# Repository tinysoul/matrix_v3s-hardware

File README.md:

# matrix_v3s-hardware

#### 介绍
一个简单的全志 V3s 开发板，使用 KiCad 设计。（谨慎参考，尚未验证，待更新）

#### 使用说明

配合 my_kicad_lib (也可不用)，直接用 KiCad 打开。

#### 参与贡献

1.  Fork 本仓库
2.  新建 Feat_xxx 分支
3.  提交代码
4.  新建 Pull Request

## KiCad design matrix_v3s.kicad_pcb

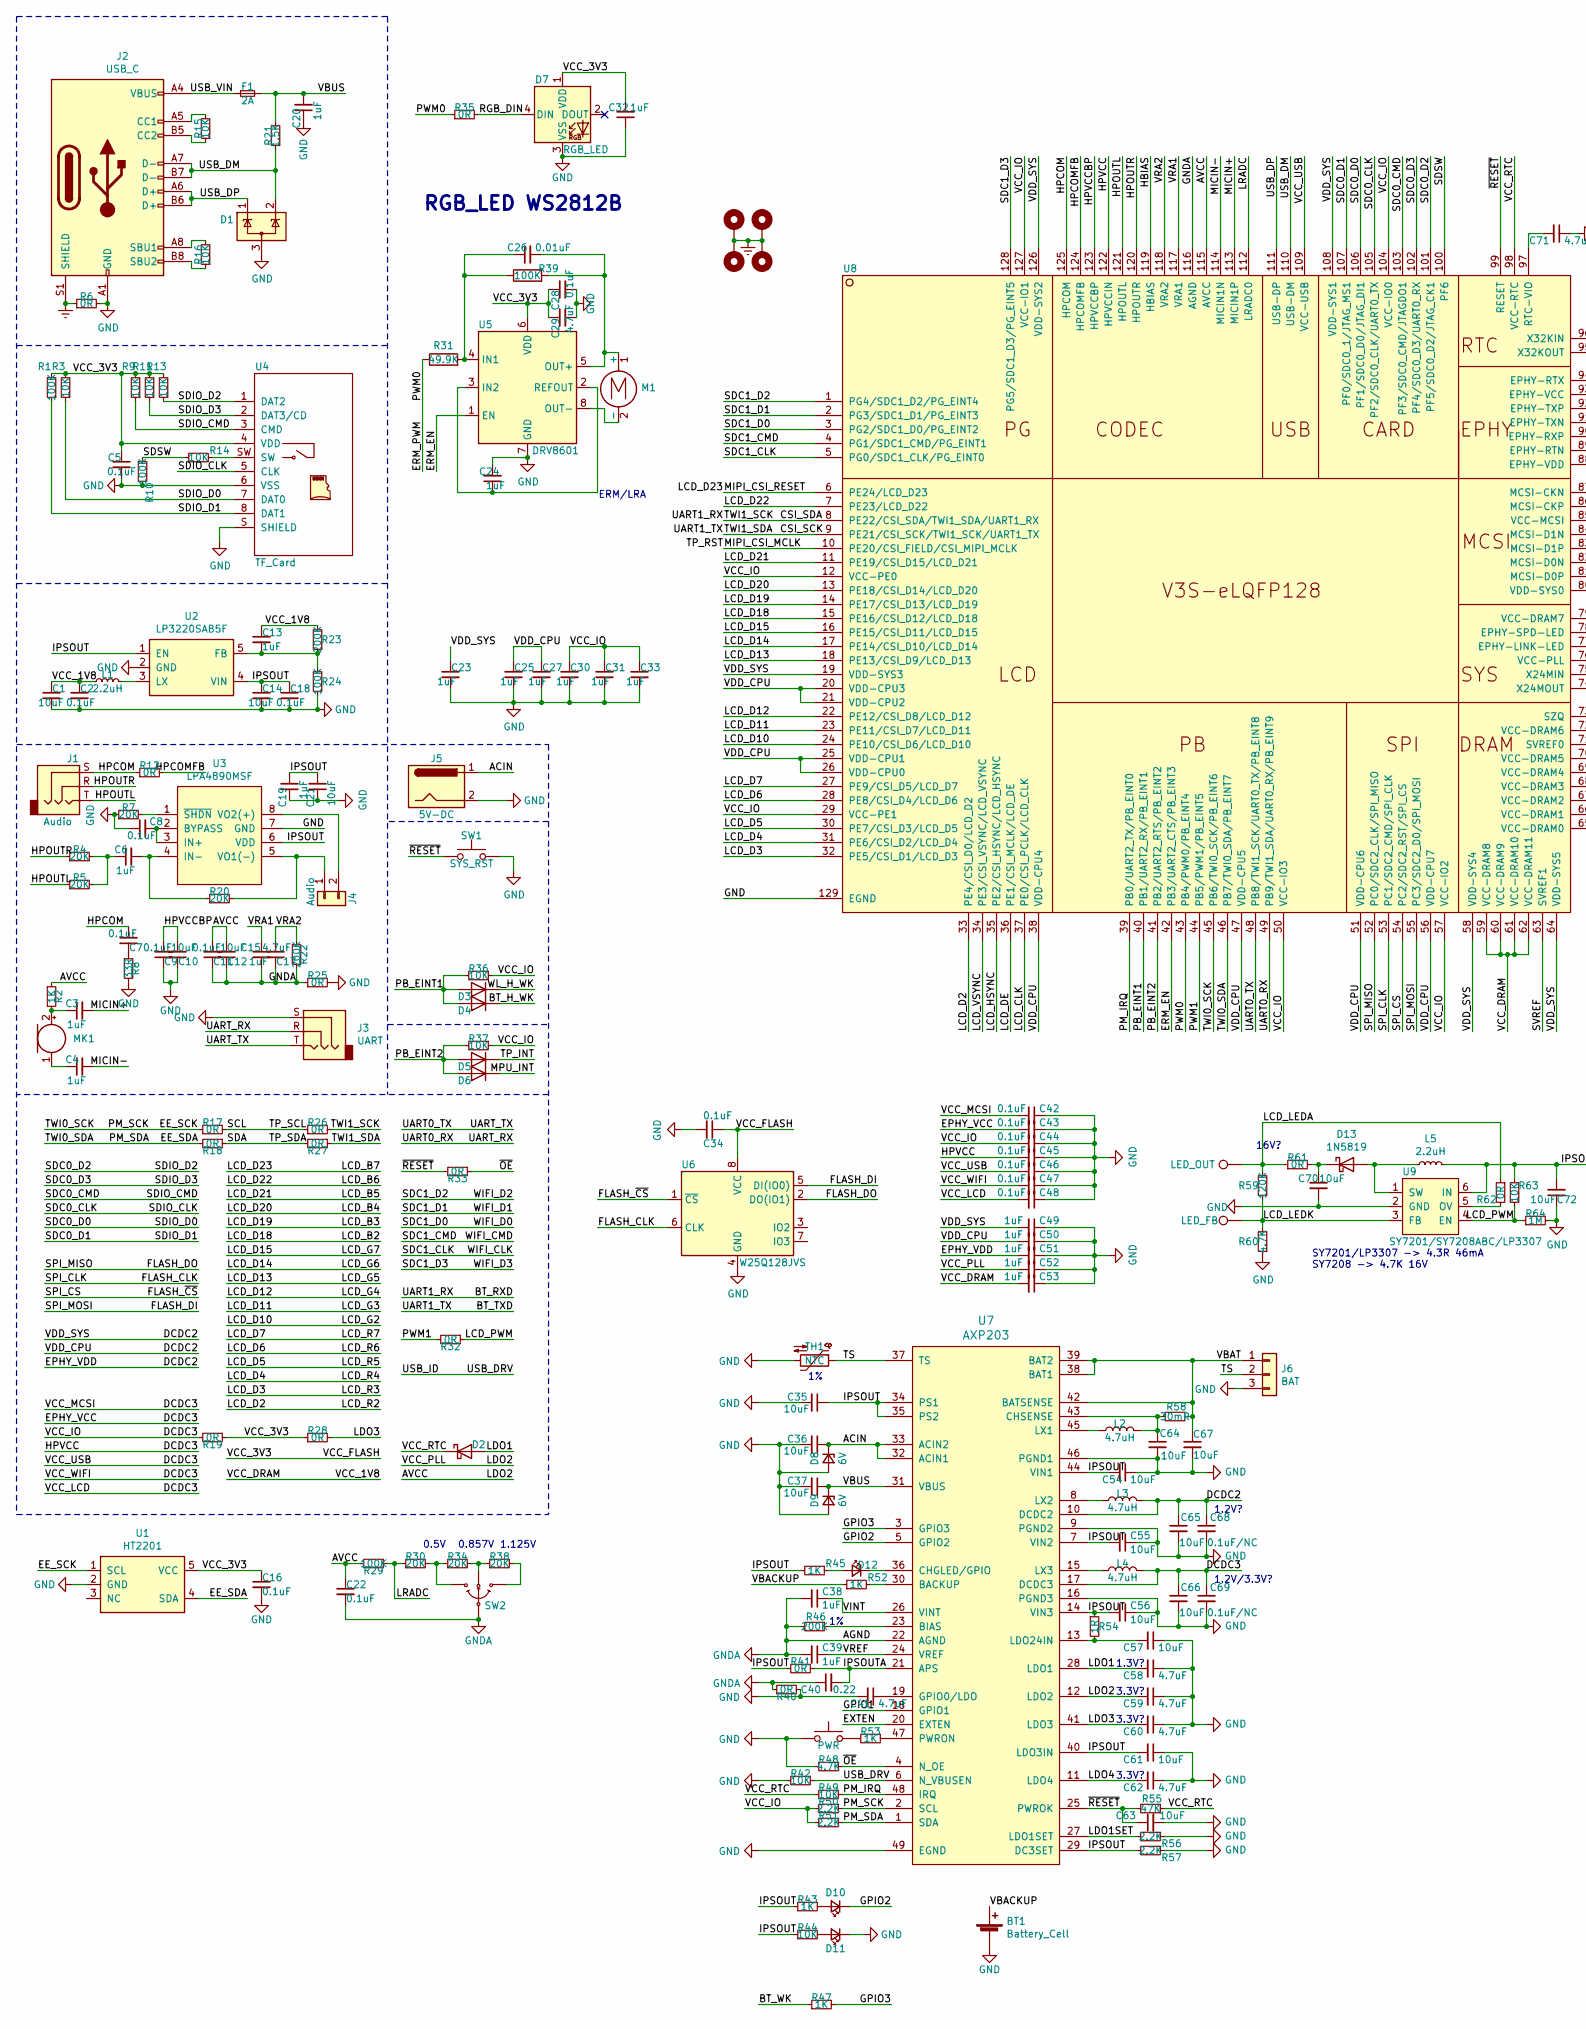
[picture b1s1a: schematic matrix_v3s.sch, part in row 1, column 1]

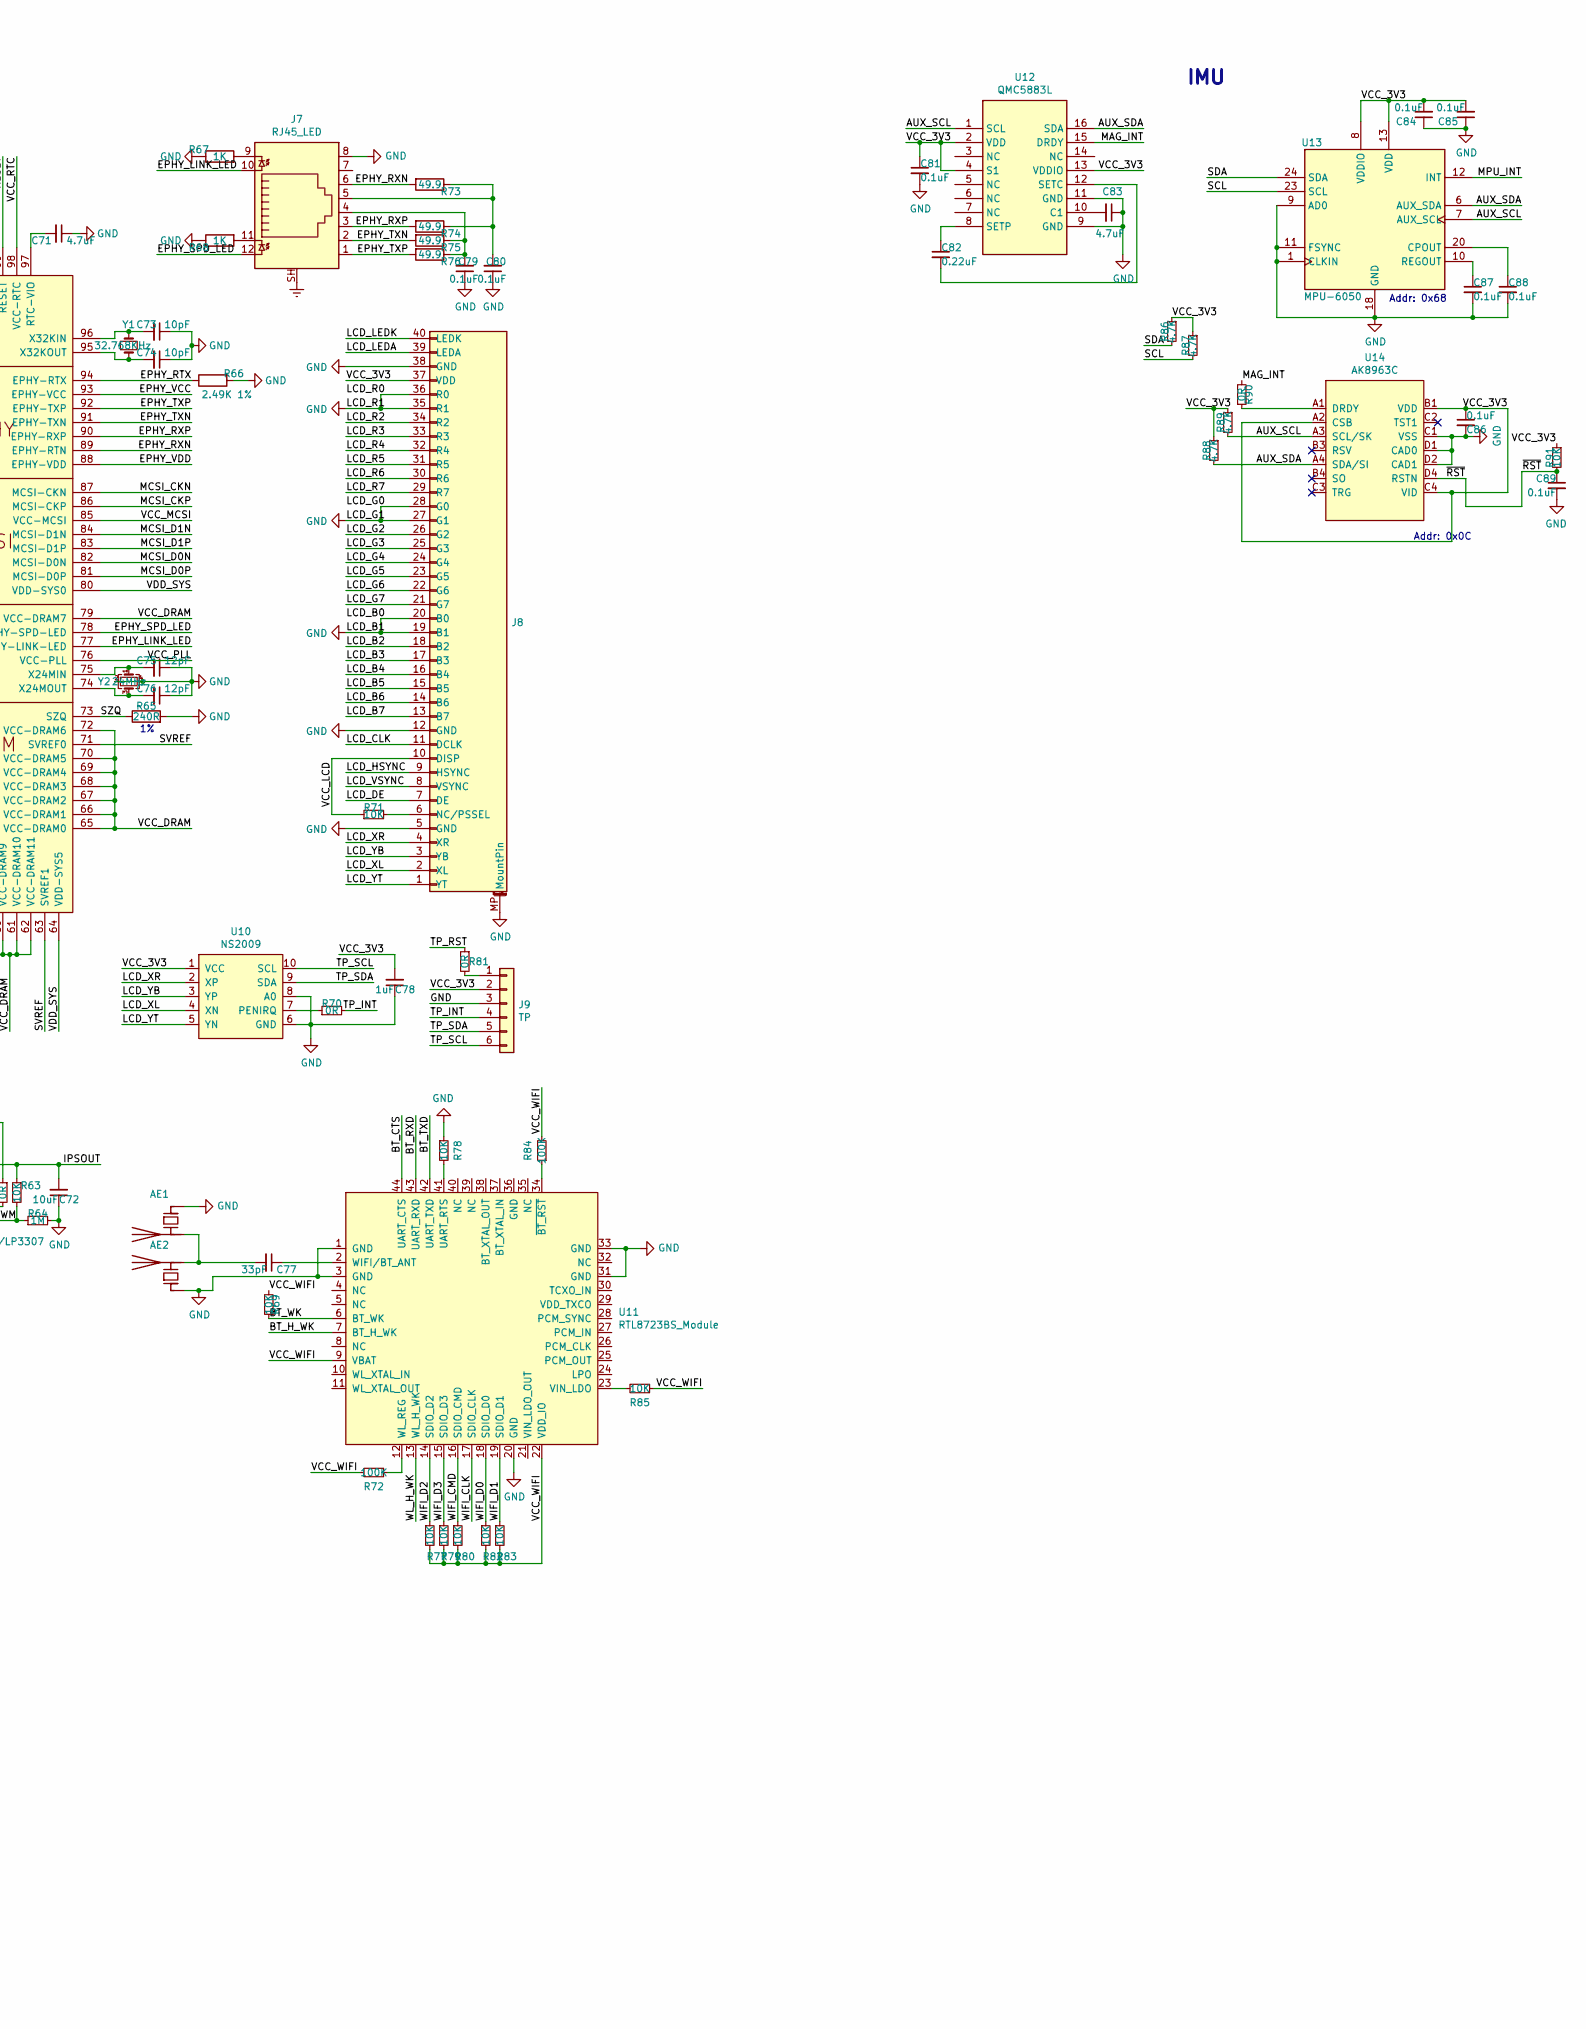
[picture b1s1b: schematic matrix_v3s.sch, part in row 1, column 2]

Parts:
AE1: Antenna_Chip; Texas_SWRA117D_2.4GHz_Left
AE2: Antenna_Chip; Johanson_2450AT43F0100
BT1: Battery_Cell; BatteryHolder_Keystone_1060_1x2032
C1, C10, C12, C14, C21, C35, C36, C37, C54, C55, C56, C57, C61, C63, C64, C65, C66, C67, C70, C72: 10uF; C_0603_1608Metric
C2, C5, C7, C8, C9, C11, C16, C18, C22, C28, C34, C42, C43, C44, C45, C46, C47, C48, C79, C80, C81, C84, C85, C86, C87, C88, C89: 0.1uF; C_0402_1005Metric
C3, C4, C6, C13, C15, C19, C20, C23, C24, C25, C27, C30, C31, C32, C33, C38, C39, C49, C50, C51, C52, C53, C78: 1uF; C_0402_1005Metric
C17, C29, C41, C58, C59, C60, C62, C71, C83: 4.7uF; C_0603_1608Metric
C26: 0.01uF; C_0402_1005Metric
C40: 0.22; C_0402_1005Metric
C68, C69: 0.1uF/NC; C_0402_1005Metric
C73, C74: 10pF; C_0603_1608Metric
C75, C76: 12pF; C_0603_1608Metric
C77: 33pF; C_0603_1608Metric
C82: 0.22uF; C_0402_1005Metric
D1: ESD; SOT-23
D2, D13: 1N5819; D_SOD-323
D3, D4, D5, D6: 1N4148; D_SOD-323
D7: RGB_LED; RGB3535
D8, D9: 6V; D_SOD-323
D10, D11: LED_Small; LED_0603_1608Metric
D12: CHGLED; D_0603_1608Metric
F1: 2A; Fuse_0805_2012Metric_Pad1.15x1.40mm_HandSolder
H1, H2, H3, H4: MountingHole_Pad; MountingHole_3.2mm_M3_Pad_Via
J1: Audio; Jack_3.5mm_PJ320B_SMT
J2: USB_C; USB_C_Receptacle_XKB_U262-16XN-4BVC11
J3: UART; Jack_3.5mm_PJ320B_SMT
J4: Audio; JST_SH_BM02B-SRSS-TB_1x02-1MP_P1.00mm_Vertical
J5: 5V-DC; BarrelJack_Horizontal
J6: BAT; JST_SH_SM03B-SRSS-TB_1x03-1MP_P1.00mm_Horizontal
J7: RJ45_LED; RJ45_Amphenol_RJHSE538X
J8: LCD_RGB_40P; Hirose_FH12-40S-0.5SH_1x40-1MP_P0.50mm_Horizontal
J9: TP; FH12-6S-1.0SH_1x6-1MP_P1.0mm_Horizontal
L1, L5: 2.2uH; L_1008_2520Metric
L2, L3, L4: 4.7uH; L_1008_2520Metric
M1: Motor_DC; JST_SH_SM02B-SRSS-TB_1x02-1MP_P1.00mm_Horizontal
MK1: Microphone; Microphone_4.5x2.2mm
R1, R10, R24, R29, R39, R72, R84: 100K; R_0402_1005Metric
R2, R43, R45, R47, R52, R53, R67, R68: 1K; R_0402_1005Metric
R3, R9, R11, R13, R14, R15, R16, R36, R37, R42, R44, R49, R63, R69, R71, R77, R78, R79, R80, R82, R83, R85, R91: 10K; R_0402_1005Metric
R4, R5, R7, R20, R30, R34, R38: 20K; R_0402_1005Metric
R6, R12, R17, R18, R19, R25, R26, R27, R28, R32, R33, R35, R40, R41, R62, R70, R81, R90: 0R; R_0402_1005Metric
R8: 33R; R_0402_1005Metric
R21: 1.5K; R_0402_1005Metric
R22, R23, R46: 200K; R_0402_1005Metric
R31: 49.9K; R_0402_1005Metric
R48, R60, R86, R87, R88, R89: 4.7K; R_0402_1005Metric
R50, R51, R56, R57: 2.2K; R_0402_1005Metric
R54: 1R; R_0402_1005Metric
R55: 47K; R_0402_1005Metric
R58: 30mR; R_0603_1608Metric
R59: 120K; R_0402_1005Metric
R61: 0R; R_0603_1608Metric
R64: 1M; R_0402_1005Metric
R65: 240R; R_0402_1005Metric
R66: 2.49K 1%; R_0402_1005Metric
R73, R74, R75, R76: 49.9; R_0402_1005Metric
SW1: SYS_RST; Key_Small_4P
SW2: SW_Thumbwheel_3ch
SW3: PWR; Key_Small_4P
TH1: NTC; R_0603_1608Metric
TP1: LED_OUT; TestPoint_Pad_D1.0mm
TP2: LED_FB; TestPoint_Pad_D1.0mm
U1: HT2201; SOT-23-5
U2: LP3220SAB5F; SOT-23-5
U3: LPA4890MSF; MSOP-8_3x3mm_P0.65mm
U4: TF_Card; TF_Card_Receptacle_Mini
U5: DRV8601; Texas_S-PVSON-N8_ThermalVias
U6: W25Q128JVS; WSON-8_8x6mm
U7: AXP203; QFN-48_EP_6x6_Pitch0.4mm_Handsoldering
U8: V3S; V3S_LQFP-128_14x14_Pitch0.4mm
U9: SY7201/SY7208ABC/LP3307; SOT-23-6_Handsoldering
U10: NS2009; MSOP-10_3x3mm_P0.5mm
U11: RTL8723BS_Module
U12: QMC5883L; LGA-16_3x3mm_P0.5mm_Handsoldering
U13: MPU-6050; QFN-24_4x4_Pitch0.5mm_NoEP_Handsoldering
U14: AK8963C; BGA-16_4x4_1.6x1.6mm
Y1: 32.768KHz; Crystal_SMD_2012-2Pin_2.0x1.2mm_HandSoldering
Y2: 24MHz; Crystal_SMD_3225-4Pin_3.2x2.5mm

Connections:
/ACIN: C36.1, D8.1 (K), J5.1, U7.32 (ACIN1), U7.33 (ACIN2)
/AUX_SCL: R89.2, U12.1 (SCL), U13.7 (AUX_SCL), U14.A3 (SCL/SK)
/AUX_SDA: R88.2, U12.16 (SDA), U13.6 (AUX_SDA), U14.A4 (SDA/SI)
/AVCC: C11.2, C12.2, C22.1, C52.2, C59.2, R2.1, R29.2, U7.12 (LDO2), U8.76 (VCC-PLL), U8.115 (AVCC)
/BT_CTS: U11.44 (UART_CTS)
/BT_H_WK: D4.1 (K), U11.7 (BT_H_WK)
/BT_RXD: R26.2, U8.8 (PE22/CSI_SDA/TWI1_SDA/UART1_RX), U11.43 (UART_RXD)
/BT_TXD: R27.1, U8.9 (PE21/CSI_SCK/TWI1_SCK/UART1_TX), U11.42 (UART_TXD)
/BT_WK: R47.1, R69.1, U11.6 (BT_WK)
/DCDC2: C23.1, C25.1, C27.1, C49.2, C50.2, C51.2, C65.1, C68.1, L3.2, U7.10 (DCDC2), U8.19 (VDD-SYS3), U8.20 (VDD-CPU3), U8.21 (VDD-CPU2), U8.25 (VDD-CPU1), U8.26 (VDD-CPU0), U8.38 (VDD-CPU4), U8.47 (VDD-CPU5), U8.51 (VDD-CPU6), U8.56 (VDD-CPU7), U8.58 (VDD-SYS4), U8.64 (VDD-SYS5), U8.80 (VDD-SYS0), U8.88 (EPHY-VDD), U8.108 (VDD-SYS1), U8.126 (VDD-SYS2)
/DCDC3: C30.1, C31.1, C33.1, C42.2, C43.2, C44.2, C45.2, C46.2, C47.2, C48.2, C66.1, C69.1, J8.10 (DISP), L4.2, R19.2, R36.1, R37.1, R50.2, R51.2, R69.2, R71.1, R72.2, R77.2, R79.2, R80.2, R82.2, R83.2, R84.2, R85.1, U7.17 (DCDC3), U8.12 (VCC-PE0), U8.29 (VCC-PE1), U8.50 (VCC-IO3), U8.57 (VCC-IO2), U8.85 (VCC-MCSI), U8.93 (EPHY-VCC), U8.104 (VCC-IO0), U8.109 (VCC-USB), U8.122 (HPVCCIN), U8.127 (VCC-IO1), U11.9 (VBAT), U11.22 (VDD_IO)
/EE_SCK: R17.1, R50.1, U1.1 (SCL), U7.2 (SCL), U8.45 (PB6/TWI0_SCK/PB_EINT6)
/EE_SDA: R18.2, R51.1, U1.4 (SDA), U7.1 (SDA), U8.46 (PB7/TWI0_SDA/PB_EINT7)
/EPHY_LINK_LED: J7.10, U8.77 (EPHY-LINK-LED)
/EPHY_RTX: R66.1, U8.94 (EPHY-RTX)
/EPHY_RXN: J7.6, R73.2, U8.89 (EPHY-RTN)
/EPHY_RXP: J7.3, R74.2, U8.90 (EPHY-RXP)
/EPHY_SPD_LED: J7.12, U8.78 (EPHY-SPD-LED)
/EPHY_TXN: J7.2, R75.2, U8.91 (EPHY-TXN)
/EPHY_TXP: J7.1, R76.2, U8.92 (EPHY-TXP)
/ERM_EN: U5.1 (EN), U8.42 (PB3/UART2_CTS/PB_EINT3)
/ERM_PWM: R31.1, R35.1, U8.43 (PB4/PWM0/PB_EINT4)
/EXTEN: U7.20 (EXTEN)
/FLASH_CLK: U6.6 (CLK), U8.53 (PC1/SDC2_CMD/SPI_CLK)
/FLASH_DI: U6.5 (DI(IO0)), U8.55 (PC3/SDC2_D0/SPI_MOSI)
/FLASH_DO: U6.2 (DO(IO1)), U8.52 (PC0/SDC2_CLK/SPI_MISO)
/FLASH_~CS: U6.1 (~CS), U8.54 (PC2/SDC2_RST/SPI_CS)
/GPIO1: U7.18 (GPIO1)
/GPIO2: D10.1 (K), U7.5 (GPIO2)
/GPIO3: R47.2, U7.3 (GPIO3)
/HBIAS: U8.119 (HBIAS)
/HPCOM: C7.2, J1.S, R12.1, U8.125 (HPCOM)
/HPCOMFB: R12.2, U8.124 (HPCOMFB)
/HPOUTL: J1.T, R5.1, U8.121 (HPOUTL)
/HPOUTR: J1.R, R4.1, U8.120 (HPOUTR)
/HPVCCBP: C9.2, C10.2, U8.123 (HPVCCBP)
/IPSOUT: C14.1, C18.1, C19.2, C21.2, C35.1, C54.2, C55.2, C56.2, C61.2, C72.2, L5.2, R41.2, R43.1, R44.1, R45.2, R54.1, R57.2, R63.1, U2.1 (EN), U2.4 (VIN), U3.6 (VDD), U7.7 (VIN2), U7.14 (VIN3), U7.29 (DC3SET), U7.34 (PS1), U7.35 (PS2), U7.40 (LDO3IN), U7.44 (VIN1), U9.6 (IN)
/IPSOUTA: C40.2, R41.1, U7.21 (APS)
/LCD_B2: J8.18 (B2), U8.15 (PE16/CSI_D12/LCD_D18)
/LCD_B3: J8.17 (B3), U8.14 (PE17/CSI_D13/LCD_D19)
/LCD_B4: J8.16 (B4), U8.13 (PE18/CSI_D14/LCD_D20)
/LCD_B5: J8.15 (B5), U8.11 (PE19/CSI_D15/LCD_D21)
/LCD_B6: J8.14 (B6), U8.7 (PE23/LCD_D22)
/LCD_B7: J8.13 (B7), U8.6 (PE24/LCD_D23)
/LCD_CLK: J8.11 (DCLK), U8.37 (PE0/CSI_PCLK/LCD_CLK)
/LCD_D2: J8.34 (R2), U8.33 (PE4/CSI_D0/LCD_D2)
/LCD_D3: J8.33 (R3), U8.32 (PE5/CSI_D1/LCD_D3)
/LCD_D4: J8.32 (R4), U8.31 (PE6/CSI_D2/LCD_D4)
/LCD_D5: J8.31 (R5), U8.30 (PE7/CSI_D3/LCD_D5)
/LCD_D6: J8.30 (R6), U8.28 (PE8/CSI_D4/LCD_D6)
/LCD_D7: J8.29 (R7), U8.27 (PE9/CSI_D5/LCD_D7)
/LCD_D10: J8.26 (G2), U8.24 (PE10/CSI_D6/LCD_D10)
/LCD_D11: J8.25 (G3), U8.23 (PE11/CSI_D7/LCD_D11)
/LCD_D12: J8.24 (G4), U8.22 (PE12/CSI_D8/LCD_D12)
/LCD_D13: J8.23 (G5), U8.18 (PE13/CSI_D9/LCD_D13)
/LCD_D14: J8.22 (G6), U8.17 (PE14/CSI_D10/LCD_D14)
/LCD_D15: J8.21 (G7), U8.16 (PE15/CSI_D11/LCD_D15)
/LCD_DE: J8.7 (DE), U8.36 (PE1/CSI_MCLK/LCD_DE)
/LCD_HSYNC: J8.9 (HSYNC), U8.35 (PE2/CSI_HSYNC/LCD_HSYNC)
/LCD_LEDA: J8.39 (LEDA), R59.2, R61.1, R62.1, TP1.1
/LCD_LEDK: J8.40 (LEDK), R59.1, R60.2, TP2.1, U9.3 (FB)
/LCD_PWM: R32.1, R63.2, R64.1, U9.4 (EN)
/LCD_VSYNC: J8.8 (VSYNC), U8.34 (PE3/CSI_VSYNC/LCD_VSYNC)
/LCD_XL: J8.2 (XL), U10.4 (XN)
/LCD_XR: J8.4 (XR), U10.2 (XP)
/LCD_YB: J8.3 (YB), U10.3 (YP)
/LCD_YT: J8.1 (YT), U10.5 (YN)
/LDO1: C58.2, D2.2 (A), U7.28 (LDO1)
/LDO1SET: R56.2, U7.27 (LDO1SET)
/LDO3: C60.2, R28.2, U7.41 (LDO3)
/LDO4: C62.2, U7.11 (LDO4)
/LRADC: R29.1, R30.1, U8.112 (LRADC0)
/MAG_INT: R90.2, U12.15 (DRDY)
/MCSI_CKN: U8.87 (MCSI-CKN)
/MCSI_CKP: U8.86 (MCSI-CKP)
/MCSI_D0N: U8.82 (MCSI-D0N)
/MCSI_D0P: U8.81 (MCSI-D0P)
/MCSI_D1N: U8.84 (MCSI-D1N)
/MCSI_D1P: U8.83 (MCSI-D1P)
/MICIN+: C3.2, U8.113 (MICIN1P)
/MICIN-: C4.2, U8.114 (MICIN1N)
/MIPI_CSI_MCLK: R81.1, U8.10 (PE20/CSI_FIELD/CSI_MIPI_MCLK)
/MPU_INT: D6.1 (K), U13.12 (INT)
/PB_EINT1: D3.2 (A), D4.2 (A), R36.2, U8.40 (PB1/UART2_RX/PB_EINT1)
/PB_EINT2: D5.2 (A), D6.2 (A), R37.2, U8.41 (PB2/UART2_RTS/PB_EINT2)
/PM_IRQ: R49.1, U7.48 (IRQ), U8.39 (PB0/UART2_TX/PB_EINT0)
/PWM1: R32.2, U8.44 (PB5/PWM1/PB_EINT5)
/RGB_DIN: D7.4 (DIN), R35.2
/SCL: J9.6, R17.2, R26.1, R87.2, U10.10 (SCL), U13.23 (SCL)
/SDA: J9.5, R18.1, R27.2, R86.2, U10.9 (SDA), U13.24 (SDA)
/SDC0_CLK: U4.5 (CLK), U8.105 (PF2/SDC0_CLK/UART0_TX)
/SDC0_CMD: R9.1, U4.3 (CMD), U8.103 (PF3/SDC0_CMD/JTAGDO1)
/SDC0_D0: R3.1, U4.7 (DAT0), U8.106 (PF1/SDC0_D0/JTAG_DI1)
/SDC0_D1: R1.1, U4.8 (DAT1), U8.107 (PF0/SDC0_1/JTAG_MS1)
/SDC0_D2: R13.1, U4.1 (DAT2), U8.101 (PF5/SDC0_D2/JTAG_CK1)
/SDC0_D3: R11.1, U4.2 (DAT3/CD), U8.102 (PF4/SDC0_D3/UART0_RX)
/SDC1_CLK: U8.5 (PG0/SDC1_CLK/PG_EINT0), U11.17 (SDIO_CLK)
/SDC1_CMD: R80.1, U8.4 (PG1/SDC1_CMD/PG_EINT1), U11.16 (SDIO_CMD)
/SDC1_D0: R82.1, U8.3 (PG2/SDC1_D0/PG_EINT2), U11.18 (SDIO_D0)
/SDC1_D1: R83.1, U8.2 (PG3/SDC1_D1/PG_EINT3), U11.19 (SDIO_D1)
/SDC1_D2: R77.1, U8.1 (PG4/SDC1_D2/PG_EINT4), U11.14 (SDIO_D2)
/SDC1_D3: R79.1, U8.128 (PG5/SDC1_D3/PG_EINT5), U11.15 (SDIO_D3)
/SDSW: R10.1, R14.1, U8.100 (PF6)
/SVREF: U8.63 (SVREF1), U8.71 (SVREF0)
/SZQ: R65.1, U8.73 (SZQ)
/TP_INT: D5.1 (K), J9.4, R70.2
/TS: J6.2, TH1.1, U7.37 (TS)
/UART0_RX: J3.R, U8.49 (PB9/TWI1_SDA/UART0_RX/PB_EINT9)
/UART0_TX: J3.T, U8.48 (PB8/TWI1_SCK/UART0_TX/PB_EINT8)
/USB_DM: D1.2 (K), J2.A7 (D-), J2.B7 (D-), R21.1, U8.110 (USB-DM)
/USB_DP: D1.1 (K), J2.A6 (D+), J2.B6 (D+), U8.111 (USB-DP)
/USB_DRV: R42.1, U7.6 (N_VBUSEN)
/USB_VIN: F1.1, J2.A4 (VBUS), J2.A9 (VBUS), J2.B4 (VBUS), J2.B9 (VBUS)
/VBACKUP: BT1.1 (+), R52.1
/VBAT: C67.1, J6.1, R58.1, U7.38 (BAT1), U7.39 (BAT2), U7.42 (BATSENSE)
/VBUS: C20.2, C37.1, D9.1 (K), F1.2, R21.2, U7.31 (VBUS)
/VCC_1V8: C1.1, C2.1, C13.1, C53.2, L1.1, R23.2, U8.59 (VCC-DRAM8), U8.60 (VCC-DRAM9), U8.61 (VCC-DRAM10), U8.62 (VCC-DRAM11), U8.65 (VCC-DRAM0), U8.66 (VCC-DRAM1), U8.67 (VCC-DRAM2), U8.68 (VCC-DRAM3), U8.69 (VCC-DRAM4), U8.70 (VCC-DRAM5), U8.72 (VCC-DRAM6), U8.79 (VCC-DRAM7)
/VCC_3V3: C5.1, C16.1, C28.1, C29.1, C32.2, C34.1, C78.2, C81.1, C84.2, C85.2, C86.1, D7.1 (VDD), J8.37 (VDD), J9.2, R1.2, R3.2, R9.2, R11.2, R13.2, R19.1, R28.1, R86.1, R87.1, R88.1, R89.1, R91.1, U1.5 (VCC), U4.4 (VDD), U5.6 (VDD), U6.8 (VCC), U10.1 (VCC), U12.2 (VDD), U12.4 (S1), U12.13 (VDDIO), U13.8 (VDDIO), U13.13 (VDD), U14.A2 (CSB), U14.B1 (VDD), U14.C4 (VID)
/VCC_RTC: D2.1 (K), R49.2, R55.1, U8.98 (VCC-RTC)
/VINT: C38.1, U7.26 (VINT)
/VRA1: C15.1, U8.117 (VRA1)
/VRA2: C17.2, R22.1, U8.118 (VRA2)
/VREF: C39.1, U7.24 (VREF)
/WL_H_WK: D3.1 (K), U11.13 (WL_H_WK)
/~OE: R33.1, R48.1, U7.4 (N_OE)
/~RESET: C63.1, R33.2, R55.2, SW1.1, U7.25 (PWROK), U8.99 (RESET)
/~RST: C89.1, R91.2, U14.D4 (RSTN)
Earth: H1.1, H2.1, H3.1, H4.1, J2.S1 (SHIELD), J7.SH, R6.1
GND: AE1.1 (FEED), AE2.1 (FEED), BT1.2 (-), C1.2, C2.2, C5.2, C8.1, C9.1, C10.1, C14.2, C16.2, C18.2, C19.1, C20.1, C21.1, C23.2, C24.2, C25.2, C27.2, C28.2, C29.2, C30.2, C31.2, C32.1, C33.2, C34.2, C35.2, C36.2, C37.2, C41.2, C42.1, C43.1, C44.1, C45.1, C46.1, C47.1, C48.1, C49.1, C50.1, C51.1, C52.1, C53.1, C54.1, C55.1, C56.1, C57.1, C58.1, C59.1, C60.1, C61.1, C62.1, C63.2, C64.2, C65.2, C66.2, C67.2, C68.2, C69.2, C70.2, C71.1, C72.1, C73.1, C74.1, C75.1, C76.1, C78.1, C79.1, C80.1, C81.2, C83.1, C84.1, C85.1, C86.2, C87.2, C88.2, C89.2, D1.3 (A), D7.3 (VSS), D8.2 (A), D9.2 (A), D11.1 (K), J2.A1 (GND), J2.A12 (GND), J2.B1 (GND), J2.B12 (GND), J3.S, J5.2, J6.3, J7.8, J8.5 (GND), J8.12 (GND), J8.19 (B1), J8.20 (B0), J8.27 (G1), J8.28 (G0), J8.35 (R1), J8.36 (R0), J8.38 (GND), J8.MP (MountPin), J9.3, R6.2, R7.1, R8.2, R10.2, R24.1, R25.2, R40.2, R42.2, R48.2, R56.1, R57.1, R60.1, R64.2, R65.2, R66.2, R67.1, R68.1, R78.1, SW1.2, SW3.1, TH1.2, U1.2 (GND), U2.2 (GND), U3.7 (GND), U4.6 (VSS), U4.S (SHIELD), U5.7 (GND), U5.9 (TH_PAD), U6.4 (GND), U7.9 (PGND2), U7.16 (PGND3), U7.46 (PGND1), U7.49 (EGND), U8.129 (EGND), U9.2 (GND), U10.6 (GND), U10.8 (A0), U11.1 (GND), U11.3 (GND), U11.20 (GND), U11.31 (GND), U11.33 (GND), U12.9 (GND), U12.11 (GND), U13.1 (CLKIN), U13.9 (AD0), U13.11 (FSYNC), U13.18 (GND), U14.C1 (VSS), U14.D1 (CAD0), U14.D2 (CAD1), Y2.2, Y2.4
GNDA: C11.1, C12.1, C15.2, C17.1, C22.2, C38.2, C39.2, C40.1, R22.2, R25.1, R40.1, R46.2, SW2.C, U7.22 (AGND), U8.116 (AGND)
unnamed: AE1.2 (PCB_Trace), AE2.2 (PCB_Trace), C77.2
unnamed: C3.1, MK1.2 (+), R2.2
unnamed: C4.1, MK1.1 (-)
unnamed: C6.1, R4.2, R5.2
unnamed: C6.2, R20.1, U3.4 (IN-)
unnamed: C7.1, R8.1
unnamed: C8.2, U3.2 (BYPASS), U3.3 (IN+)
unnamed: C13.2, R23.1, R24.2, U2.5 (FB)
unnamed: C24.1, U5.2 (REFOUT), U5.3 (IN2)
unnamed: C26.1, R31.2, R39.1, U5.4 (IN1)
unnamed: C26.2, M1.1 (+), R39.2, U5.5 (OUT+)
unnamed: C41.1, U7.19 (GPIO0/LDO)
unnamed: C57.2, R54.2, U7.13 (LDO24IN)
unnamed: C64.1, L2.2, R58.2, U7.43 (CHSENSE)
unnamed: C70.1, D13.1 (K), R61.2
unnamed: C71.2, U8.97 (RTC-VIO)
unnamed: C73.2, U8.96 (X32KIN), Y1.1
unnamed: C74.2, U8.95 (X32KOUT), Y1.2
unnamed: C75.2, U8.75 (X24MIN), Y2.1
unnamed: C76.2, U8.74 (X24MOUT), Y2.3
unnamed: C77.1, U11.2 (WIFI/BT_ANT)
unnamed: C79.2, J7.4, R75.1, R76.1
unnamed: C80.2, J7.5, R73.1, R74.1
unnamed: C82.1, U12.8 (SETP)
unnamed: C82.2, U12.12 (SETC)
unnamed: C83.2, U12.10 (C1)
unnamed: C87.1, U13.10 (REGOUT)
unnamed: C88.1, U13.20 (CPOUT)
unnamed: D10.2 (A), R43.2
unnamed: D11.2 (A), R44.2
unnamed: D12.1 (K), U7.36 (CHGLED/GPIO)
unnamed: D12.2 (A), R45.1
unnamed: D13.2 (A), L5.1, U9.1 (SW)
unnamed: J2.A5 (CC1), R15.2
unnamed: J2.A8 (SBU1), R16.2
unnamed: J2.B5 (CC2), R15.1
unnamed: J2.B8 (SBU2), R16.1
unnamed: J4.1, R20.2, U3.5 (VO1(-))
unnamed: J4.2, U3.8 (VO2(+))
unnamed: J7.9, R67.2
unnamed: J7.11, R68.2
unnamed: J8.6 (NC/PSSEL), R71.2
unnamed: J9.1, R81.2
unnamed: L1.2, U2.3 (LX)
unnamed: L2.1, U7.45 (LX1)
unnamed: L3.1, U7.8 (LX2)
unnamed: L4.1, U7.15 (LX3)
unnamed: M1.2 (-), U5.8 (OUT-)
unnamed: R7.2, U3.1 (~SHDN)
unnamed: R14.2, U4.SW
unnamed: R30.2, R34.1, SW2.2
unnamed: R34.2, R38.1, SW2.T
unnamed: R38.2, SW2.1
unnamed: R46.1, U7.23 (BIAS)
unnamed: R52.2, U7.30 (BACKUP)
unnamed: R53.1, U7.47 (PWRON)
unnamed: R53.2, SW3.2
unnamed: R62.2, U9.5 (OV)
unnamed: R70.1, U10.7 (PENIRQ)
unnamed: R72.1, U11.12 (WL_REG)
unnamed: R78.2, U11.41 (UART_RTS)
unnamed: R84.1, U11.34 (~BT_RST)
unnamed: R85.2, U11.23 (VIN_LDO)
unnamed: R90.1, U14.A1 (DRDY)

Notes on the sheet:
RGB_LED WS2812B
ERM/LRA
Addr: 0x68
IMU
Addr: 0x0C
SY7201/LP3307 -> 4.3R 46mA SY7208 -> 4.7K 16V
16V?
1.125V
0.857V
0.5V
1.2V?
1.2V/3.3V?
3.3V?
1.3V?

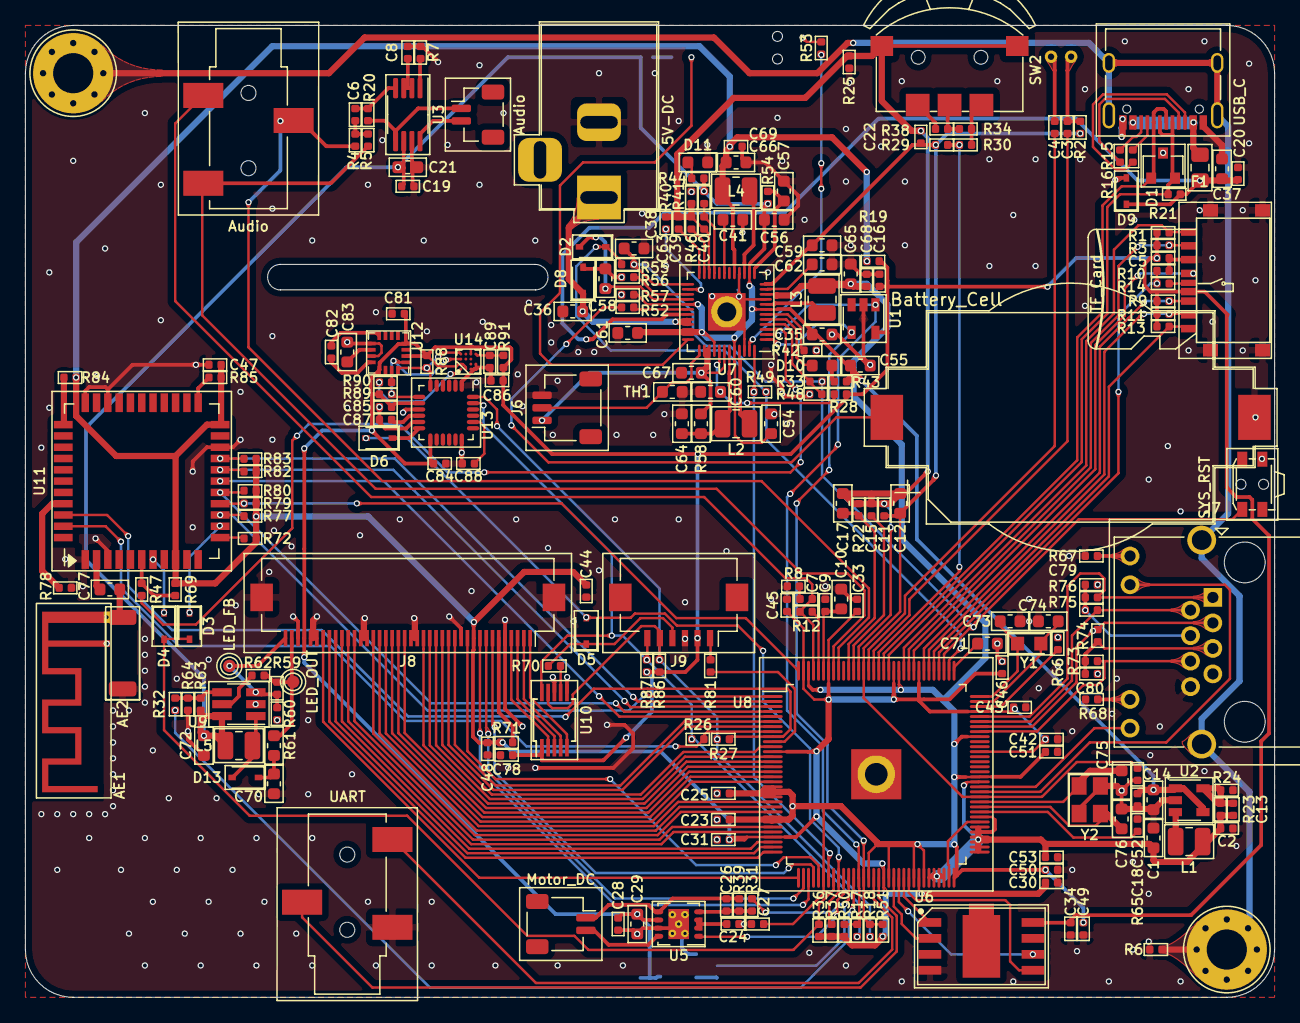
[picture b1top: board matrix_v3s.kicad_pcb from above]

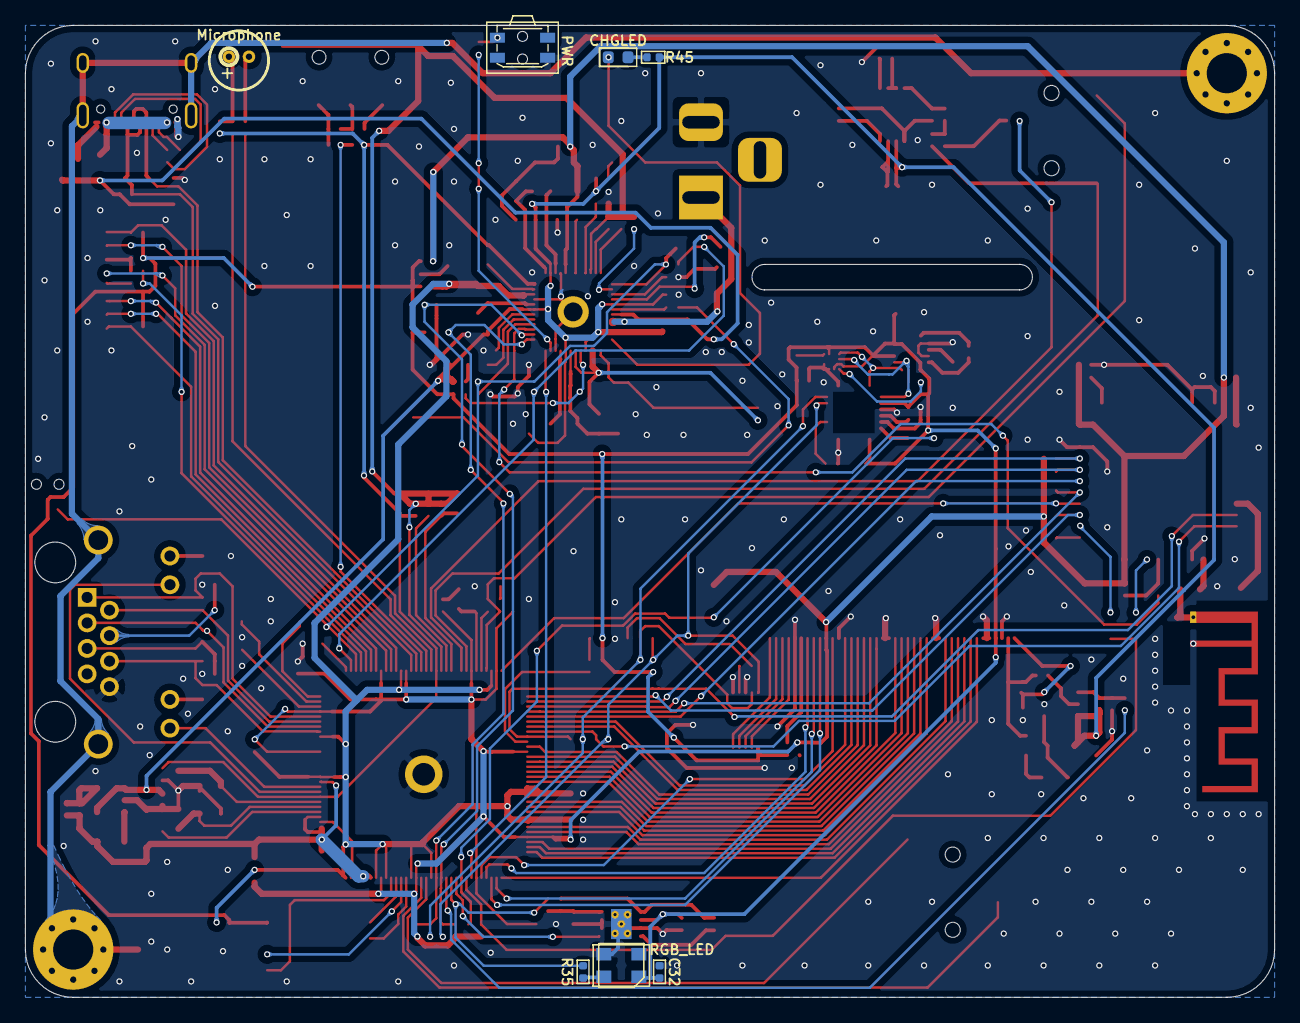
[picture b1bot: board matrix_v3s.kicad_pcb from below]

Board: 2 copper layers, 99.6 x 77.5 mm, 237 parts (7 on the bottom side), 184 nets.

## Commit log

2020-07-11 v0.0.1
